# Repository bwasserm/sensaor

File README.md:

# senSAOr - a sensor SAO

A Simple Add-On (SAO) for a conference badge with a modular sensor port and a reactive multicolor LED.

# Project Goals
* Design and make an SAO in time for Hackaday Supercon 2024
* Make it inexpensive enough and simple enough to make a bunch and trade with others
* Blinky, but more interesting than only blinky
* Cool design
* If writing firmware, write it in Rust
* If using a microcontroller, use RISC-V

# High Level Design

SAO is a microcontroller that reads a sensor from an input pin, and uses the measured voltage to drive the color/brightness/pattern of an LED.
Create ports for multiple different sensors to be used, with the ability to solder in different signal conditioning.
Use ID pins or a solderable resistors to tell firmware how to "read" the sensor and drive the LED in response.

# Expected Behaviors

The inputs are read to set the color of the bottom LED. Every cycle, the colors are clocked one LED up the board, and potentially out to an attached strand of addition WS2812s attached at the top. All inputs are read in [0V, 3.3V] as low to high.

## Red/Green/Blue
These inputs are read to set the base intensity of the LEDs accordingly.

## Speed
This sets the delay between update cycles from fast (low) to slow (high). Full low has no added delay between cycles, and full high has about 1s between cycles.

## Shape
This is the mixture ration between setting the output intensity of the colors based directly on the input (low) vs also mixing in a sine wave (high) to the brightness (off to the intensity set by the color input).

## Phase
When mixing in the sine wave, this delays the mix of the sine wave applied to green and blue relative to red. Low is the same phase of sine wave is applied to all three colors, and high is about 120 degrees of delay to green and 240 degrees of delay to blue.

## ID pins
Currently unused

## I2C
Currently unused. Set as high impedance inputs.

## GPIO\[12\]
Currently unused. Set as high impedance inputs.

## More WS2812
Connect more Neopixels here to continue clocking out colors beyond the three on the SAO.

## SAOAO
Hopefully "standard" SAOAO port to connect an SAOAO.

# Resources
* [Shitty Add-On Version 2.0 Specification](https://docs.google.com/document/u/0/d/1EJqvkkLMAPsQ9VWF5A4elWoi0qMlKyr5Giw5rqRmtnM/mobilebasic?pli=1)
* [Opensource toolchain for WCH CH32V RISC-V 32bit MCU](https://github.com/cjacker/opensource-toolchain-ch32v)
* [ch32-hal](https://github.com/ch32-rs/ch32-hal)
* [Rust on the CH32V003](https://noxim.xyz/blog/rust-ch32v003/)
* [CH32V00X-hal](https://github.com/ch32-rs/ch32v00x-hal)
* [wlink application](https://github.com/ch32-rs/wlink)
* [wlink with CH32V003](https://github.com/ch32-rs/wlink/blob/main/docs/CH32V003.md)
* [CH32V003F4P6-R0 image](https://github.com/openwch/ch32v003/blob/main/SCHPCB/CH32V003F4P6-R0-1v1/image/board1.jpg)
* [CH32V003F4P6-R0 schematic](https://github.com/openwch/ch32v003/blob/main/SCHPCB/CH32V003F4P6-R0-1v1/SCH_PCB/CH32V003F4P6-R0-1v1.pdf)
* [ch32v003.svd](https://github.com/ch32-rs/ch32-rs/blob/main/svd/fixed/ch32v003.svd)
* [CH32V003 Reference Manual](https://www.wch-ic.com/downloads/file/358.html)
* [CH32V003 Processor Manual](https://www.wch-ic.com/downloads/file/369.html)
* [CH32V003 Datasheet](https://www.wch-ic.com/downloads/file/359.html)
* [RISC-V Spec](https://riscv.org/wp-content/uploads/2019/12/riscv-spec-20191213.pdf)
* [SAOAO](https://hackaday.io/project/198060-yo-dawg-sao-introducing-saoao)

# Implementation blog

## Getting rust to build

Getting rust to compile was mostly following the [Rust on the CH32V003](https://noxim.xyz/blog/rust-ch32v003/) blog, with some off-roading. LLVM had already
picked up the support for `rv32ec` (the `e` extension is the core `i` architecture, but with 16 registers instead of 32 for smaller silicon), but rustc didn't know
the riscv32ec-unknown-none-elf target. Eventually I figured out I didn't need to make the hack to rustc either, if I provided a target .json file to build against.
However, having a local copy of llvm and the binary tools was useful, such as for llvm-objdump.

Eventually I found that much of the work on the blog was "done" in the [CH32V00X-hal](https://github.com/ch32-rs/ch32v00x-hal) project, so I cloned that next to this project.
To avoid copying files, I hacked this to link to it. .cargo/config.toml points the target to `ch32v00x-hal/riscv32ec-unknown-none-elf.json`. The target json I copied from the noxim
blog is included for good measure.

I also found that the `-Tmemory.x` and `-Tlink.x` arguments got redundant with the CH32V00X-hal repo and build.rs (adding that repo as a Cargo dep changes things), so it may
require some experimentation.

Note on `memory.x`:
Looking at the memory map, it appears that program flash is a 16KB block starting at address `0x0800 0000`. However, ch32v00x-hal and the noxim blog both define
`FLASH (rx) : ORIGIN = 0x00000000, LENGTH = 16K` at address `0x0000 0000`, which is the `Aliased to Flash or system memory depending on software configuration` block of a much
larger size. This block defaults to flash, and the program counter (`pc`) will default to address `0x0000 0000` when the chip boots. So even though it seems unintuitive, set the `FLASH`
address in `memory.x` to be 0x0. 

I went down an exploratory path using `ch32v00x-hal/link-qkv2.x` instead of finding `link.x`, which required modifying `INCLUDE device.x` to become `INCLUDE svd2rs/device.x`,
after also `cargo install svd2rust`, and running it on [cj32v003.svd](https://github.com/ch32-rs/ch32-rs/blob/main/svd/fixed/ch32v003.svd) to generate `device.x`. However, after
adding in [CH32V00X-hal](https://github.com/ch32-rs/ch32v00x-hal), I found I didn't need this.

## Getting blinky to run

I'm playing with the CH32V003F4P6-R0 dev board, pictured [here](https://github.com/openwch/ch32v003/blob/main/SCHPCB/CH32V003F4P6-R0-1v1/image/board1.jpg), and referencing
the [schematic](https://github.com/openwch/ch32v003/blob/main/SCHPCB/CH32V003F4P6-R0-1v1/SCH_PCB/CH32V003F4P6-R0-1v1.pdf) as well was super handy. Especially because I tried using
PA1 as an arbitrary GPIO pin choice, but it is already tied to the oscillator.

I used the [wlink](https://github.com/ch32-rs/wlink) application with the WLinkE . It turned out to be surprisingly easy to run and use to dump registers and flash. It's not even
necessary to convert the elf file produced by cargo/rustc into an Intel Hex file or a bin first.

```
cargo install wlink
```

* Programming command: `sudo ~/.cargo/bin/wlink -v --chip ch32v003 flash target/riscv32ec-unknown-none-elf/debug/sensaor`
* Get registers command: `sudo ~/.cargo/bin/wlink -v --chip ch32v003 regs`
* Dump the beginning of program flash: `sudo ~/.cargo/bin/wlink -v --chip ch32v003 dump 0x00000000 400`

The sudo is becuase I'm too lazy to figure out which group to add myself to to get permissions to talk to the programmer.

`wlink` also has a serial terminal functionality that works with the WLinkE debugger I'm using. However, my WLinkE isn't showing up as a serial device (`/dev/ttyASM0` or similar),
so I can't connect to that. I'm guessing it's a udev rule I need to update, since `lsusb` indicates multiple modem/serial interfaces on the USB device. Probably an Arch (BTW) config
issue on my end.

Using the LEDs on the dev board, it's important to set the GPIO pins into open drain mode, not push-pull. With the extra resistors from push-pull, not enough current flows to turn
on the LEDs (since they already have resistors installed inline).

### WLink on Windows

On my Windows 10/11 machines, I was getting `Error: USB error: Entity not found` errors when trying to run `wlink status`. This is because the wlink doesn't activate the correct drivers by default.

* See this [github issue](https://github.com/ch32-rs/wlink/issues/5) for an example
* Install [zadig](https://zadig.akeo.ie/)
* Select `WCH-Link (Interface 0)` and install the driver `WinUSB`.

## Reading the ADC to modify the blink

First, I moved the binaries into src/bin/ so I could build multiple at once, and therefore make things easier to have multiple apps in work.

The greatest challenge reading the ADC was finding the right part of the HAL to use. Eventually I found `ch32v00x-hal/src/adc.rs` `OneShot::read()`, but due to not knowing rust's import system well enough, spent way too long getting it to build. Through help, the answer is adding `embedded-hal-02` as a dependency, and `use embedded_hal_02::adc::OneShot;`. While I don't have a great analog source yet, the blink rate does apear to change when I touch the input pin, so I think it might be working.

## Driving the Neopixels

I wanted to use a Neopixel (WS2811/WS2812) library to drive them, but those rely on a timer or SPI implementation for the chip. The hal I'm using for the CH32V003 doesn't implement SPI. After getting annoyed with the traits required to get the existing timer library to work, I figured implementing enough of SPI to write would be easier. With enough time with the manual, and some C examples of setting up SPI on this chip to compare which bits are set in the control registers, I got my neopixel string to change colors.

# Programming tips

Including any `println!()` calls without having the debugger connected and watching the serial port will cause the application to block upon a print.

With serial console:

```
cargo b --release; wlink -v --chip ch32v003 flash .\target\riscv32ec-unknown-none-elf\release\sao --enable-sdi-print --watch-serial
```

Without serial console:

```
cargo b --release; wlink -v --chip ch32v003 flash .\target\riscv32ec-unknown-none-elf\release\sao
```

Note that using `println!()` when sdi print is not enabled or the debugger is not watching serial will cause the program to lock up at the first `println!()`.

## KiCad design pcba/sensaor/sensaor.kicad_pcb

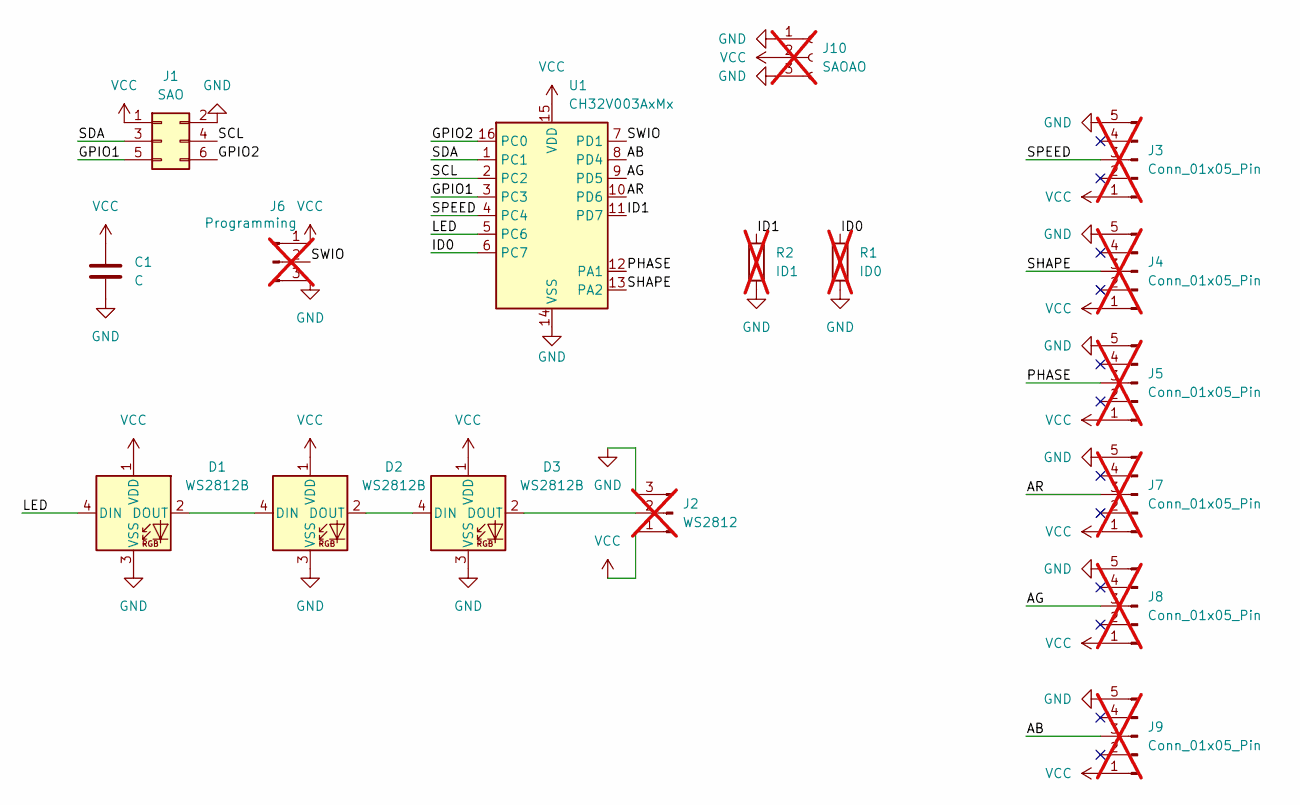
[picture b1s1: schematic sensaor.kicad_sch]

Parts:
C1: C; C_0603_1608Metric_Pad1.08x0.95mm_HandSolder
D1, D2, D3: WS2812B; LED_WS2812B_PLCC4_5.0x5.0mm_P3.2mm
J1: SAO; IDC-Header_2x03_P2.54mm_Vertical
J2: WS2812; PinHeader_1x03_P2.54mm_Vertical; not fitted
J3, J4, J5, J7, J8, J9: Conn_01x05_Pin; PinHeader_1x05_P2.54mm_Vertical; not fitted
J6: Programming; PinHeader_1x03_P2.54mm_Vertical; not fitted
J10: SAOAO; PinHeader_1x03_P1.27mm_Vertical; not fitted
R1: ID0; C_0402_1005Metric_Pad0.74x0.62mm_HandSolder; not fitted
R2: ID1; C_0402_1005Metric_Pad0.74x0.62mm_HandSolder; not fitted
U1: CH32V003AxMx; SOP-16_3.9x9.9mm_P1.27mm

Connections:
/AB: J9.3, U1.8 (PD4)
/AG: J8.3, U1.9 (PD5)
/AR: J7.3, U1.10 (PD6)
/GPIO1: J1.5, U1.3 (PC3)
/GPIO2: J1.6, U1.16 (PC0)
/ID0: R1.1, U1.6 (PC7)
/ID1: R2.1, U1.11 (PD7)
/LED: D1.4 (DIN), U1.5 (PC6)
/PHASE: J5.3, U1.12 (PA1)
/SCL: J1.4, U1.2 (PC2)
/SDA: J1.3, U1.1 (PC1)
/SHAPE: J4.3, U1.13 (PA2)
/SPEED: J3.3, U1.4 (PC4)
/SWIO: J6.2, U1.7 (PD1)
GND: C1.2, D1.3 (VSS), D2.3 (VSS), D3.3 (VSS), J1.2, J2.3, J3.5, J4.5, J5.5, J6.3, J7.5, J8.5, J9.5, J10.1, J10.3, R1.2, R2.2, U1.14 (VSS)
unnamed: D1.2 (DOUT), D2.4 (DIN)
unnamed: D2.2 (DOUT), D3.4 (DIN)
unnamed: D3.2 (DOUT), J2.2
VCC: C1.1, D1.1 (VDD), D2.1 (VDD), D3.1 (VDD), J1.1, J2.1, J3.1, J4.1, J5.1, J6.1, J7.1, J8.1, J9.1, J10.2, U1.15 (VDD)

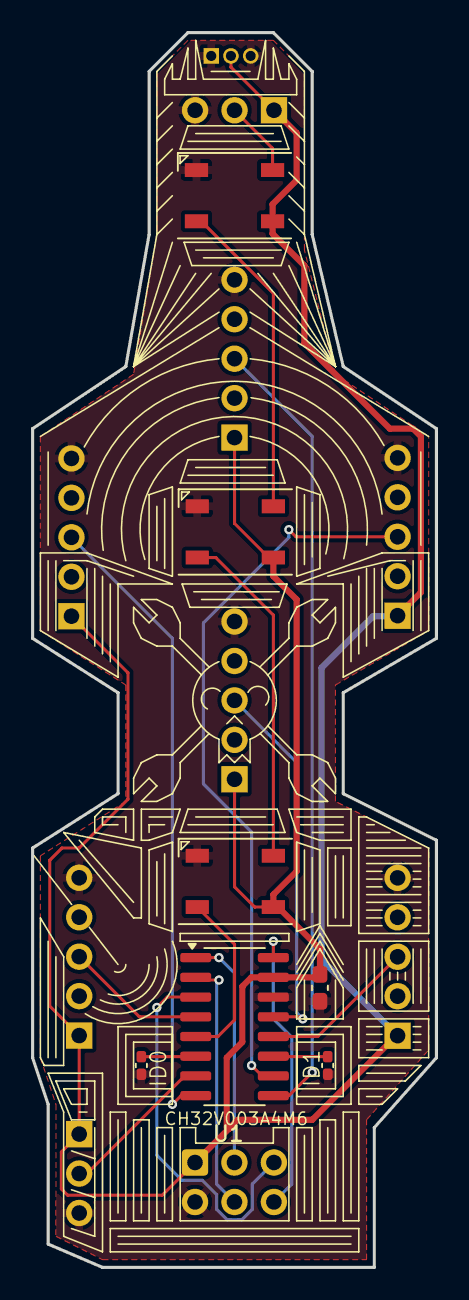
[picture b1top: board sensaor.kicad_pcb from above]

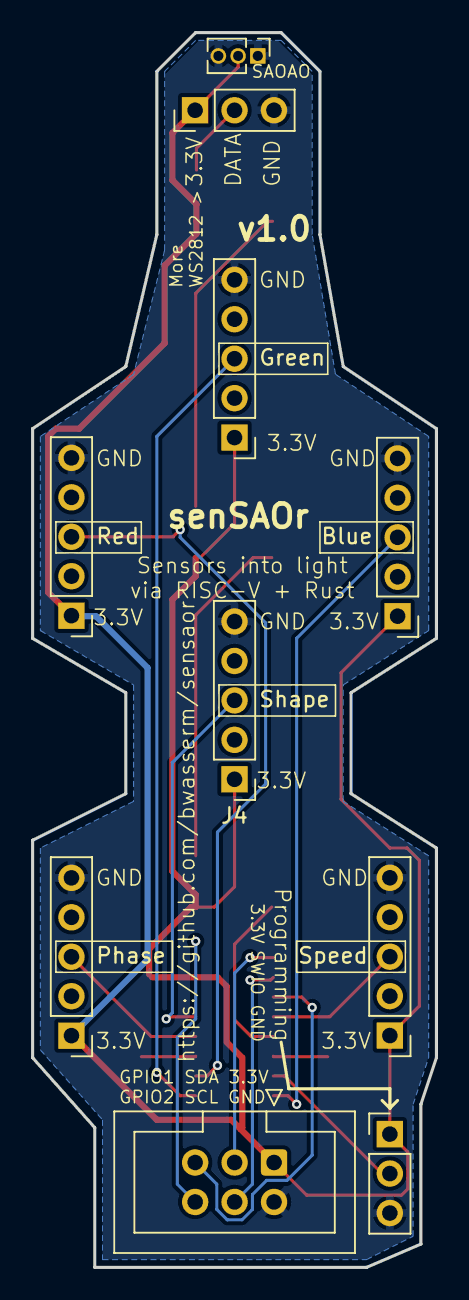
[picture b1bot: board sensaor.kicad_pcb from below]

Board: 2 copper layers, 26.0 x 79.5 mm, 17 parts (10 on the bottom side), 19 nets.

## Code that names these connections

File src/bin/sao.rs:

#![no_main]
#![no_std]

use ch32v00x_hal::i2c::{I2c, I2cConfig};
use ws2812_spi::{self, Ws2812};

use embedded_hal_02::adc::OneShot;
use embedded_hal_1::spi;

use smart_leds::{brightness, SmartLedsWrite, RGB8};

use embedded_hal_1::delay::DelayNs;
use panic_halt as _;

use ch32v00x_hal::prelude::*;
use ch32v00x_hal::println;
use ch32v00x_hal::{self as hal};

#[qingke_rt::entry]
fn main() -> ! {
    // Constrain clocking registers
    let p = ch32v0::ch32v003::Peripherals::take().unwrap();

    p.RCC
        .apb2pcenr
        .modify(|_, w| w
            .spi1en().set_bit()
            .adc1en().set_bit()
            .iopaen().set_bit()
            .iopcen().set_bit()
            .iopden().set_bit()
        );
    p.RCC.apb2prstr.modify(|_, w| w.spi1rst().set_bit());
    p.RCC.apb2prstr.modify(|_, w| w.spi1rst().clear_bit());
    p.SPI1.ctlr1.modify(|_, w| {w
        .bidimode()
            .set_bit()
        .bidioe()
            .set_bit()
        .crcen()
            .clear_bit()
        .crcnext()
            .clear_bit()
        .dff()
            .clear_bit()
        .rxonly()
            .clear_bit()
        .ssm()
            .set_bit()
        .ssi()
            .set_bit()
        .lsbfirst()
            .clear_bit()
        .spe()
            .clear_bit()
        .br()
            .variant(2_u8) // 24MHz / 8 => 3Mhz
        .mstr()
            .set_bit()
        .cpha()
            .clear_bit()
        .cpol()
            .clear_bit()
    });
    p.SPI1.ctlr1.modify(|_, w| w.spe().set_bit());
    let mut rcc = p.RCC.constrain();
    let clocks = rcc.config.freeze();

    // Get delay provider
    let mut delay = hal::delay::CycleDelay::new(&clocks);

    let gpioa = p.GPIOA.split(&mut rcc);
    let gpioc = p.GPIOC.split(&mut rcc);
    let gpiod = p.GPIOD.split(&mut rcc);

    let mut adc_red = gpiod.pd6.into_analog();
    let mut adc_green = gpiod.pd5.into_analog();
    let mut adc_blue = gpiod.pd4.into_analog();
    let mut adc_speed = gpioc.pc4.into_analog();
    let mut adc_shape = gpioa.pa2.into_analog();
    let mut adc_phase = gpioa.pa1.into_analog();
    let sda = gpioc.pc1.into_floating_input();
    let scl = gpioc.pc2.into_floating_input();
    let _mosi = gpioc
        .pc6
        .into_alternate()
        .set_speed(ch32v00x_hal::gpio::Speed::Mhz50);
    let mut _id0 = gpioc.pc7.into_pull_up_input();
    let mut _id1 = gpiod.pd7.into_pull_up_input();
    let mut _gpio1 = gpioc.pc3.into_floating_input();
    let mut _gpio2 = gpioc.pc0.into_floating_input();

    let mut adc = hal::adc::Adc::new(p.ADC1, &clocks);
    // let _i2c = I2c::i2c1(p.I2C1, scl, sda, I2cConfig::fast_mode(), &mut rcc, &clocks);
    let spi = SpiDriver::new(p.SPI1);
    let mut ws = Ws2812::new(spi);

    // let mut adc_val: u16 = adc.read(&mut pc4).unwrap();

    const NUM_LEDS: usize = 62;
    let mut led_data = [RGB8 { r: 0, g: 0, b: 0}; NUM_LEDS];
    const LEN_SINE_TABLE: usize = 256;
    let sine_table: [u32; LEN_SINE_TABLE] = [
        128, 131, 134, 137, 140, 143, 146, 149, 152, 155, 158, 162, 165, 167, 170, 173,
        176, 179, 182, 185, 188, 190, 193, 196, 198, 201, 203, 206, 208, 211, 213, 215,
        218, 220, 222, 224, 226, 228, 230, 232, 234, 235, 237, 238, 240, 241, 243, 244,
        245, 246, 248, 249, 250, 250, 251, 252, 253, 253, 254, 254, 254, 255, 255, 255,
        255, 255, 255, 255, 254, 254, 254, 253, 253, 252, 251, 250, 250, 249, 248, 246,
        245, 244, 243, 241, 240, 238, 237, 235, 234, 232, 230, 228, 226, 224, 222, 220,
        218, 215, 213, 211, 208, 206, 203, 201, 198, 196, 193, 190, 188, 185, 182, 179,
        176, 173, 170, 167, 165, 162, 158, 155, 152, 149, 146, 143, 140, 137, 134, 131,
        128, 124, 121, 118, 115, 112, 109, 106, 103, 100, 97, 93, 90, 88, 85, 82,
        79, 76, 73, 70, 67, 65, 62, 59, 57, 54, 52, 49, 47, 44, 42, 40,
        37, 35, 33, 31, 29, 27, 25, 23, 21, 20, 18, 17, 15, 14, 12, 11,
        10, 9, 7, 6, 5, 5, 4, 3, 2, 2, 1, 1, 1, 0, 0, 0,
        0, 0, 0, 0, 1, 1, 1, 2, 2, 3, 4, 5, 5, 6, 7, 9,
        10, 11, 12, 14, 15, 17, 18, 20, 21, 23, 25, 27, 29, 31, 33, 35,
        37, 40, 42, 44, 47, 49, 52, 54, 57, 59, 62, 65, 67, 70, 73, 76,
        79, 82, 85, 88, 90, 93, 97, 100, 103, 106, 109, 112, 115, 118, 121, 124
        ];
    let _adc_max: u32 = adc.max_sample().into();
    // let mut red_data: [u32; NUM_LEDS] = [0; NUM_LEDS];
    // let mut green_data: [u32; NUM_LEDS] = [0; NUM_LEDS];
    // let mut blue_data: [u32; NUM_LEDS] = [0; NUM_LEDS];
        
    // let mut data = [RGB8 { r: 0, g: 0, b: 0}; NUM_LEDS];
    // loop {
        //     for j in 0..(256 * 5) {
    //         for i in 0..NUM_LEDS {
    //             data[i] = _wheel((((i * 256) as u16 / NUM_LEDS as u16 + j as u16) & 255) as u8);
    //         }
    //         ws.write(brightness(data.iter().cloned(), 16)).unwrap();
    //         delay.delay_ms(5);
    //         println!("{} {} {}", data[0], data[1], data[2]);
    //     }
    // }
    
    // let scaling: u32 = 1;
    let mut time: u32 = 0;
    loop {
        let phase_delay_a: u32 = adc.read(&mut adc_phase).unwrap();
        let phase_delay = phase_delay_a >> 3;
        let sine_red = sine_table[time as u8 as usize];
        let sine_green = sine_table[(time + phase_delay) as u8 as usize];
        let sine_blue = sine_table[(time + 2 * phase_delay) as u8 as usize];
        let shape_val: u32 = adc.read(&mut adc_shape).unwrap();
        let dc_offset = _adc_max - shape_val;

        let red_val_a: u32 = adc.read(&mut adc_red).unwrap();
        // red_val_a = x / 1024 (x / 2^10)
        // sine_red = x / 256 (x / 2^8)
        // shape_val = x / 1024 (x / 2^10)
        // red_sine_part = x / 2^16
        let red_sine_part = (red_val_a * sine_red * shape_val) >> 12;
        // red_val_a = x / 1024 (x / 2^10)
        // dc_offset = x / 1024 (x / 2^10)
        // red_dc_part = x / 2^16
        let red_dc_part = (red_val_a * dc_offset) >> 4;
        // red_val = x / 256 (x / 2^8)
        let red_val = (red_sine_part + red_dc_part) >> 8;

        let green_val_a: u32 = adc.read(&mut adc_green).unwrap();
        let green_sine_part = (green_val_a * sine_green * shape_val) >> 12;
        let green_dc_part = (green_val_a * dc_offset) >> 4;
        let green_val = (green_sine_part + green_dc_part) >> 8;

        let blue_val_a: u32 = adc.read(&mut adc_blue).unwrap();
        let blue_sine_part = (blue_val_a * sine_blue * shape_val) >> 12;
        let blue_dc_part = (blue_val_a * dc_offset) >> 4;
        let blue_val = (blue_sine_part + blue_dc_part) >> 8;
        
        let mut delay_val: u32 = adc.read(&mut adc_speed).unwrap();
        // println!("{delay_val}");
        delay_val = (delay_val - 420) * 10;
        delay_val = delay_val.max(0).min(1000);
        let delay_ms: u32 = delay_val;

        for i in (1..NUM_LEDS).rev() {
            led_data[i] = led_data[i - 1].clone();
        }
        led_data[0] = RGB8 { r: (red_val) as u8,
                             g: (green_val) as u8,
                             b: (blue_val) as u8};
        ws.write(brightness(led_data.iter().cloned(), 32)).unwrap();
        for _ in 0..delay_ms {
            time = time.wrapping_add(1);
            delay.delay_ms(1);
        }
        // println!("{red_val_a}\t{red_val}\t{delay_val}\t{phase_delay}\t{shape_val}  {dc_offset}");
        // println!("t: {time}\nLED: {} {} {}\ndelay_ms: {delay_ms} phase: {phase_delay_a} shape: {shape_val}", led_data[0], led_data[1], led_data[2]);
    }
}

/// Input a value 0 to 255 to get a color value
/// The colours are a transition r - g - b - back to r.
fn _wheel(mut wheel_pos: u8) -> RGB8 {
    wheel_pos = 255 - wheel_pos;
    if wheel_pos < 85 {
        return (255 - wheel_pos * 3, 0, wheel_pos * 3).into();
    }
    if wheel_pos < 170 {
        wheel_pos -= 85;
        return (0, wheel_pos * 3, 255 - wheel_pos * 3).into();
    }
    wheel_pos -= 170;
    (wheel_pos * 3, 255 - wheel_pos * 3, 0).into()
}

#[derive(Debug)]
struct SpiDriver {
    spi: ch32v00x_hal::pac::SPI1,
}

impl SpiDriver {
    pub fn new(spi: ch32v00x_hal::pac::SPI1) -> Self {
        Self { spi }
    }
}

impl spi::ErrorType for SpiDriver {
    type Error = spi::ErrorKind;
}

impl spi::SpiBus for SpiDriver {
    fn read(&mut self, _words: &mut [u8]) -> Result<(), Self::Error> {
        todo!()
    }

    fn write(&mut self, words: &[u8]) -> Result<(), Self::Error> {
        while self.spi.statr.read().txe().bit_is_clear() {}
        for word in words {
            self.spi.datar.write(|w| unsafe { w.bits(*word as u32) });
        }
        Ok(())
    }

    fn transfer(&mut self, _read: &mut [u8], _write: &[u8]) -> Result<(), Self::Error> {
        todo!()
    }

    fn transfer_in_place(&mut self, _words: &mut [u8]) -> Result<(), Self::Error> {
        todo!()
    }

    fn flush(&mut self) -> Result<(), Self::Error> {
        todo!()
    }
}

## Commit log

2024-08-24 Initial commit, add README
2024-08-24 Add some text to readme
2024-09-04 Add files needed to reach blinky with docs in README
2024-09-04 Fix some readme formatting
2024-09-06 Move applications so I can build both bins. Add adc demo to practice reading the ADC, and have it change the blink rate accordingly.
2024-09-07 Update readme for adc
2024-09-18 Implement SPI and WS2812 rainbow
2024-09-18 Fix comment for clock conversion
2024-09-19 Add PCBA, needs finishing
2024-09-20 Update PCB
2024-09-22 Shrink board and fix DRC
2024-09-22 Add ground pours, update silkscreen
2024-09-22 Moving some traces
2024-09-22 Moved a dimension
2024-09-22 Updates from review feedback, shrunk board more
2024-09-27 formatting
2024-09-27 Start firmware for SAO
2024-09-28 Poking at things
2024-10-01 I think this is what I ordered as the v0.9 boards
2024-10-01 Redesign board into more of a carrier shape
2024-10-01 Fix ground plane connections
2024-10-01 Update silkscreens
2024-10-02 Improved LED driving behavior, disabled I2C
2024-10-03 Add SAOAO connector, tweak some placements
2024-10-03 Adjustments from PCBA review
2024-10-04 Making progress with sao blinky behavior
2024-10-26 More debug notes in readme, fixed math so all 6 inputs should work to set colors correctly
2024-10-26 Update and comment out debug prints, and update README with the behaviors..
2024-10-29 Some debug tips in readme
2024-10-29 Adjusted layout. Ordered 30x v1.0 boards
2024-11-02 Rescale speed for celeste
